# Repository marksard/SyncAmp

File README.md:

# Synthesizer Sync Output Voltage Amplifier

A comparator-type amplifier that provides 5V Sync voltage for small instruments such as Teenage Engineering PO-32 and Paripi Destroyer.

[blog](https://marksard.github.io/2023/02/23/make-line-mixer/)

## Usage

Connect to SyncIn from a small instrument such as Teenage Engineering PO-32, Paripi Destroyer, etc.  
From Sync Out, connect to the instrument with Sync In.  
Adjust the Threshold knob until the LED flashes moderately in time with the pulse of the Sync voltage. If it syncs, you have succeeded.  

## Spec

### Input

3.5mm phone jack (TS)  
DC input is available.  

### Thresold Setting

As known as V ref.  
Range of values 0V to 2.5V.  

### Output

3.5mm phone jack (TS)  
Range of values 0V to 4.7V.  

### Power supply

- 9V

## Schematic

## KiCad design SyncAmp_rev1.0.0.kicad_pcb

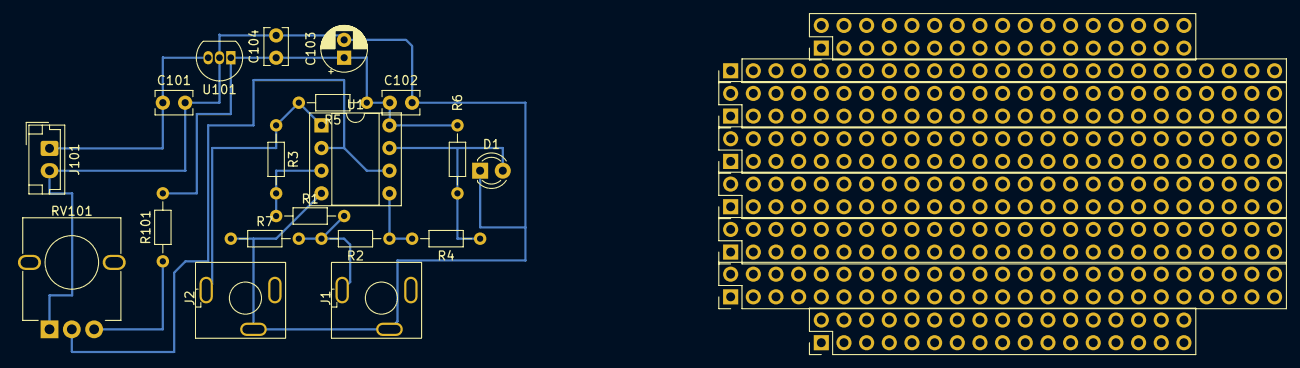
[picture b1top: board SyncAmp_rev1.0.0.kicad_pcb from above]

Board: 2 copper layers, 19 parts (0 on the bottom side), 10 nets.

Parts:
C101: 0.33u; C_Rect_L4.0mm_W2.5mm_P2.50mm
C102, C104: 0.1u; C_Rect_L4.0mm_W2.5mm_P2.50mm
C103: 47u; CP_Radial_D5.0mm_P2.00mm
D1: LED; LED_D3.0mm
J1: Sync In; MJ-355W
J2: Sync Out; MJ-355W
J101: Barrel_Jack; JST_EH_B2B-EH-A_1x02_P2.50mm_Vertical
R1, R2, R7, R101: 10k; R_Axial_DIN0204_L3.6mm_D1.6mm_P7.62mm_Horizontal
R3, R4: 10Meg; R_Axial_DIN0204_L3.6mm_D1.6mm_P7.62mm_Horizontal
R5, R6: 3k; R_Axial_DIN0204_L3.6mm_D1.6mm_P7.62mm_Horizontal
RV101: B10k; Potentiometer_THT_RK09L1140
U1: LM393; DIP-8_W7.62mm_Socket
U101: LM78L05_TO92; TO-92_Inline

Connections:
/in: J1.T, R1.2, R2.2, R7.2
/out: J2.T, R3.1, R5.2, U1.1
GND: C101.2, C102.2, C103.2, C104.2, D1.1 (K), J1.S, J2.S, J101.2, R7.1, RV101.1, U1.4 (V-), U101.2 (GND)
unnamed: C101.1, J101.1, U101.3 (VI)
unnamed: D1.2 (A), R4.1, R6.2, U1.7
unnamed: R1.1, R3.2, U1.3 (+)
unnamed: R2.1, R4.2, U1.5 (+)
unnamed: R101.1, RV101.3
VCC: C102.1, C103.1, C104.1, R5.1, R6.1, R101.2, U1.8 (V+), U101.1 (VO)
vref: RV101.2, U1.2 (-), U1.6 (-)

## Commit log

2023-03-07 move
